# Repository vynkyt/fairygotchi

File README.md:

# Fairygotchi
Tamagotchi fairy that takes care of YOU rather than you of it  (gives reminders at intervals and acts silly). 

I made this in a tamagotchi workshop and I wanted to make it because I wanted evidence that I could finish a hardware project fully from start to end. I decided on this concept of a fairy instead of a pet mainly because of the pcb art I decided to use, and on it taking care of you rather than you of it because when I was younger I had a tamagotchi I really liked but what I liked most about it was that it had a clock, so I wanted to build something useful for my first tamagotchi too :)

To use it, you press the buttons below the screen, and you'll be redirected to different screen interfaces each with different functionality (e.g. sleep screen). 

## Schematic

## PCB

## 3D Render of PCB

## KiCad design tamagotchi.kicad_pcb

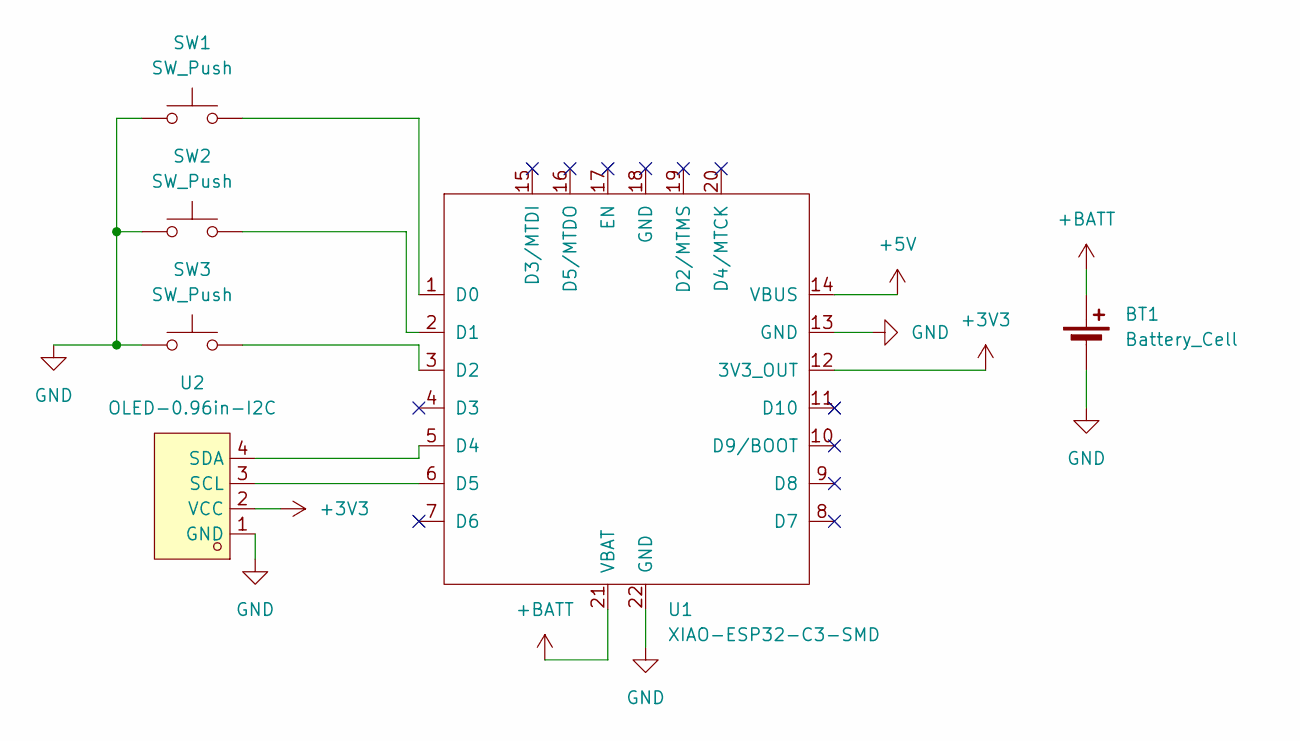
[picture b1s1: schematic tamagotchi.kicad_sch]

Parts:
BT1: Battery_Cell; PinHeader_1x02_P2.54mm_Vertical
SW1, SW2, SW3: SW_Push; SW_Cherry_MX_1.00u_PCB
U1: XIAO-ESP32-C3-SMD; XIAO-ESP32-C3
U2: OLED-0.96in-I2C; MPN HS96L03W2C03; LCSC Part C5248080

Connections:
+3V3: U1.12 (3V3_OUT), U2.2 (VCC)
+5V: U1.14 (VBUS)
+BATT: BT1.1 (+), U1.21 (VBAT)
GND: BT1.2 (-), SW1.1, SW2.1, SW3.1, U1.13 (GND), U1.22 (GND), U2.1 (GND)
unnamed: SW1.2, U1.1 (D0)
unnamed: SW2.2, U1.2 (D1)
unnamed: SW3.2, U1.3 (D2)
unnamed: U1.5 (D4), U2.4 (SDA)
unnamed: U1.6 (D5), U2.3 (SCL)

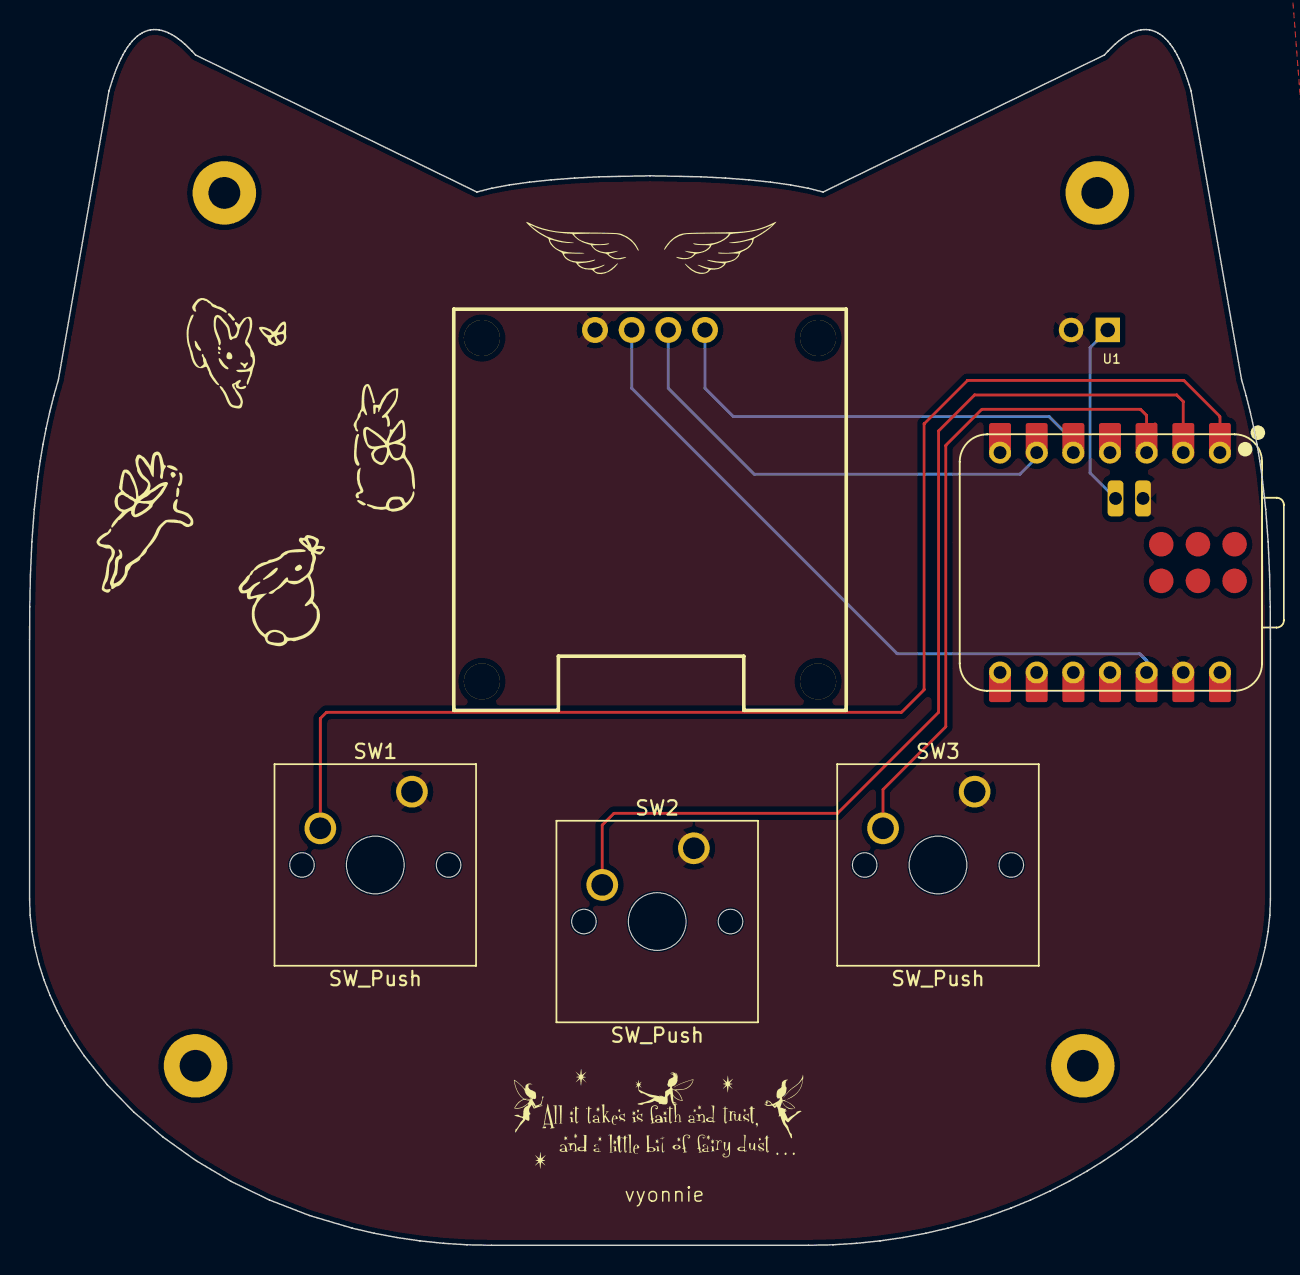
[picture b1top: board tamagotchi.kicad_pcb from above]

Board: 2 copper layers, 86.0 x 84.3 mm, 7 parts (1 on the bottom side), 8 nets.

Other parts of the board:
REF: MountingHole_2.2mm_M2_Pad
